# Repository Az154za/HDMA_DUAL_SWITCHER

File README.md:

# HDMA_DUAL_SWITCHER
This is 2 to 1 hdmi multiplexer that can switch screen visualisation between two pcs with a switch toggle using the TMDS261BPAG

# Schematic : 

# Routing :
The PCB was 4 layers 1 layer for GND , one layer for 5V

# 3D overview :

#BOM :

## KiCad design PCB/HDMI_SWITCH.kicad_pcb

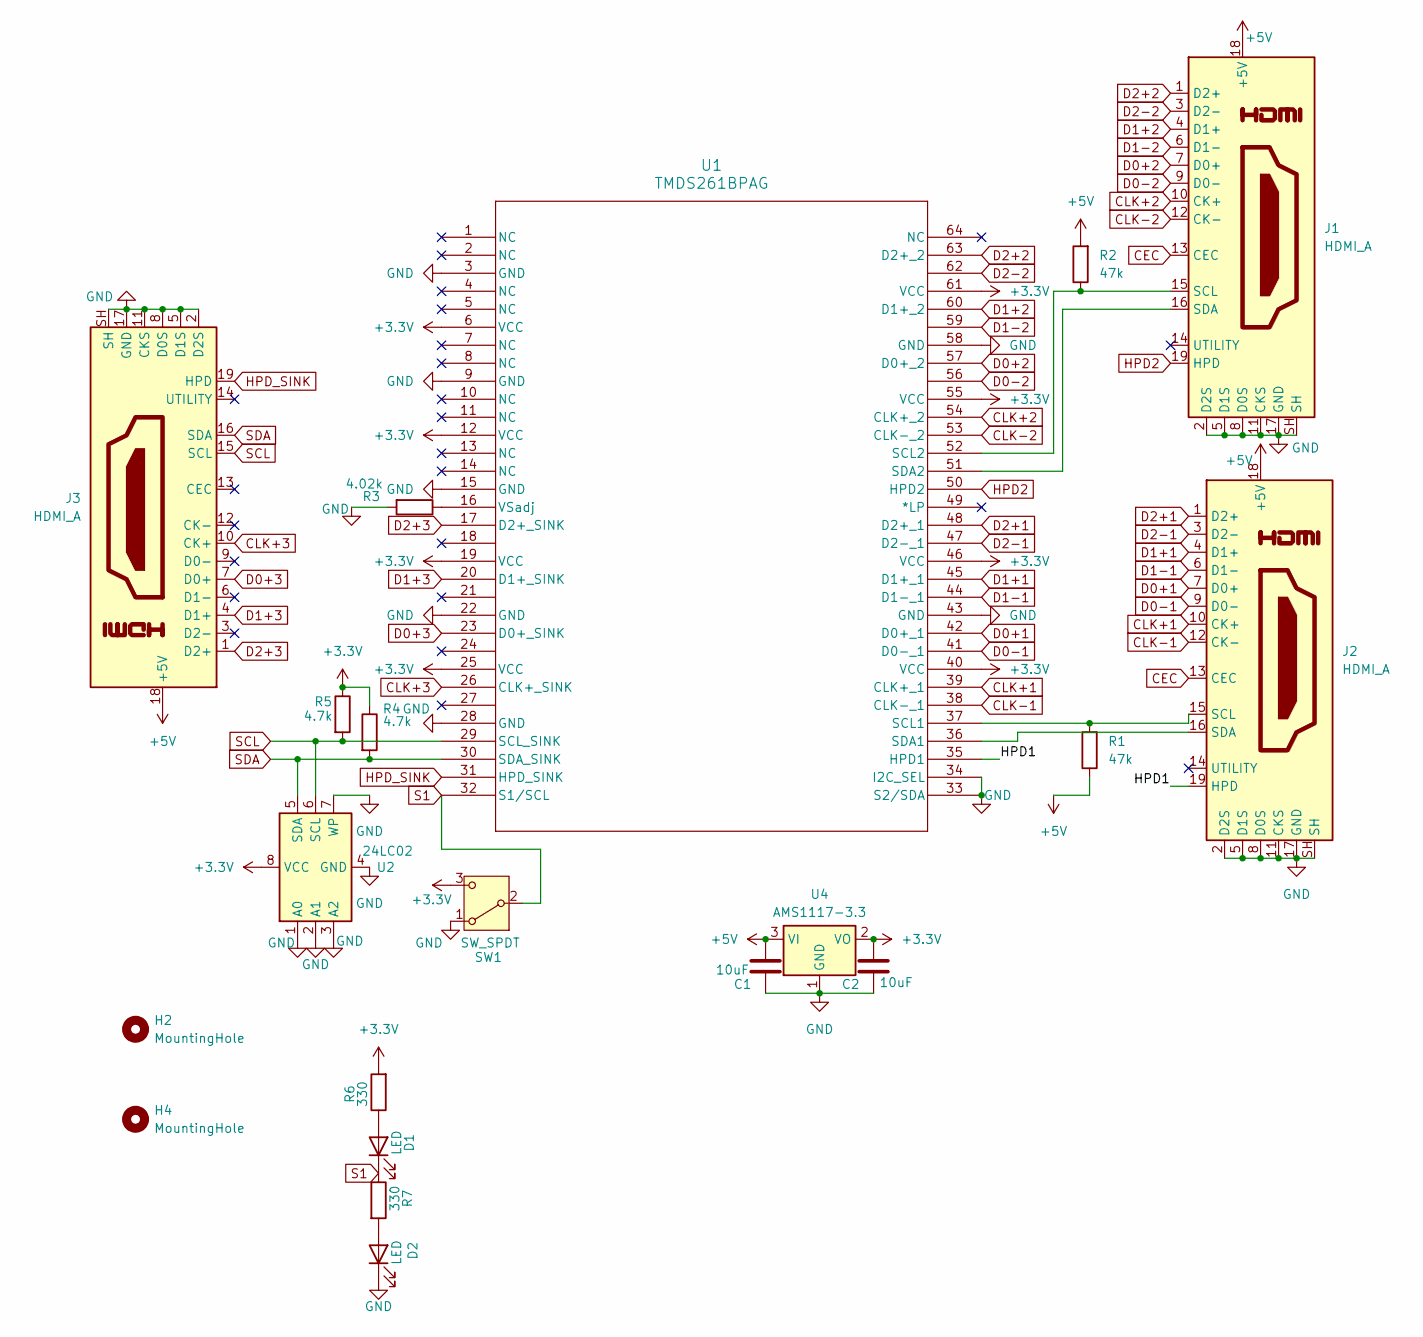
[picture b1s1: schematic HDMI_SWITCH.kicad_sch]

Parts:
C1, C2: 10uF; C_0805_2012Metric
D1, D2: LED; LED_0603_1608Metric
H2, H4: MountingHole; MountingHole_2.2mm_M2
J1, J2, J3: HDMI_A; HDMI_A_Amphenol_10029449-x01xLF_Horizontal
R1, R2: 47k; R_0402_1005Metric
R3: 4.02k; R_0402_1005Metric
R4, R5: 4.7k; R_0402_1005Metric
R6, R7: 330; R_0402_1005Metric
SW1: SW_SPDT; SW_SPDT_PCM12
U1: TMDS261BPAG; PAG64
U2: 24LC02; JEITA_SOIC-8_3.9x4.9mm_P1.27mm
U4: AMS1117-3.3; SOT-223-3_TabPin2

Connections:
+3.3V: C2.2, R4.1, R5.1, R6.2, SW1.3 (C), U1.6 (VCC), U1.12 (VCC), U1.19 (VCC), U1.25 (VCC), U1.40 (VCC), U1.46 (VCC), U1.55 (VCC), U1.61 (VCC), U2.8 (VCC), U4.2 (VO)
+5V: C1.2, J1.18 (+5V), J2.18 (+5V), J3.18 (+5V), R1.1, R2.2, U4.3 (VI)
/HPD1: J2.19 (HPD), U1.35 (HPD1)
CEC: J1.13 (CEC), J2.13 (CEC)
CLK+1: J2.10 (CK+), U1.39 (CLK+_1)
CLK+2: J1.10 (CK+), U1.54 (CLK+_2)
CLK+3: J3.10 (CK+), U1.26 (CLK+_SINK)
CLK-1: J2.12 (CK-), U1.38 (CLK-_1)
CLK-2: J1.12 (CK-), U1.53 (CLK-_2)
D0+1: J2.7 (D0+), U1.42 (D0+_1)
D0+2: J1.7 (D0+), U1.57 (D0+_2)
D0+3: J3.7 (D0+), U1.23 (D0+_SINK)
D0-1: J2.9 (D0-), U1.41 (D0-_1)
D0-2: J1.9 (D0-), U1.56
D1+1: J2.4 (D1+), U1.45 (D1+_1)
D1+2: J1.4 (D1+), U1.60 (D1+_2)
D1+3: J3.4 (D1+), U1.20 (D1+_SINK)
D1-1: J2.6 (D1-), U1.44 (D1-_1)
D1-2: J1.6 (D1-), U1.59
D2+1: J2.1 (D2+), U1.48 (D2+_1)
D2+2: J1.1 (D2+), U1.63 (D2+_2)
D2+3: J3.1 (D2+), U1.17 (D2+_SINK)
D2-1: J2.3 (D2-), U1.47 (D2-_1)
D2-2: J1.3 (D2-), U1.62
GND: C1.1, C2.1, D2.1 (K), J1.2 (D2S), J1.5 (D1S), J1.8 (D0S), J1.11 (CKS), J1.17 (GND), J1.SH, J2.2 (D2S), J2.5 (D1S), J2.8 (D0S), J2.11 (CKS), J2.17 (GND), J2.SH, J3.2 (D2S), J3.5 (D1S), J3.8 (D0S), J3.11 (CKS), J3.17 (GND), J3.SH, R3.2, SW1.1 (A), U1.3 (GND), U1.9 (GND), U1.15 (GND), U1.22 (GND), U1.28 (GND), U1.33 (S2/SDA), U1.34 (I2C_SEL), U1.43 (GND), U1.58 (GND), U2.1 (A0), U2.2 (A1), U2.3 (A2), U2.4 (GND), U2.7 (WP), U4.1 (GND)
HPD2: J1.19 (HPD), U1.50 (HPD2)
HPD_SINK: J3.19 (HPD), U1.31 (HPD_SINK)
unnamed: D1.2 (A), R6.1
unnamed: D2.2 (A), R7.2
unnamed: J1.15 (SCL), R2.1, U1.52 (SCL2)
unnamed: J1.16 (SDA), U1.51 (SDA2)
unnamed: J2.15 (SCL), R1.2, U1.37 (SCL1)
unnamed: J2.16 (SDA), U1.36 (SDA1)
unnamed: R3.1, U1.16 (VSadj)
S1: D1.1 (K), R7.1, SW1.2 (B), U1.32 (S1/SCL)
SCL: J3.15 (SCL), R5.2, U1.29 (SCL_SINK), U2.6 (SCL)
SDA: J3.16 (SDA), R4.2, U1.30 (SDA_SINK), U2.5 (SDA)

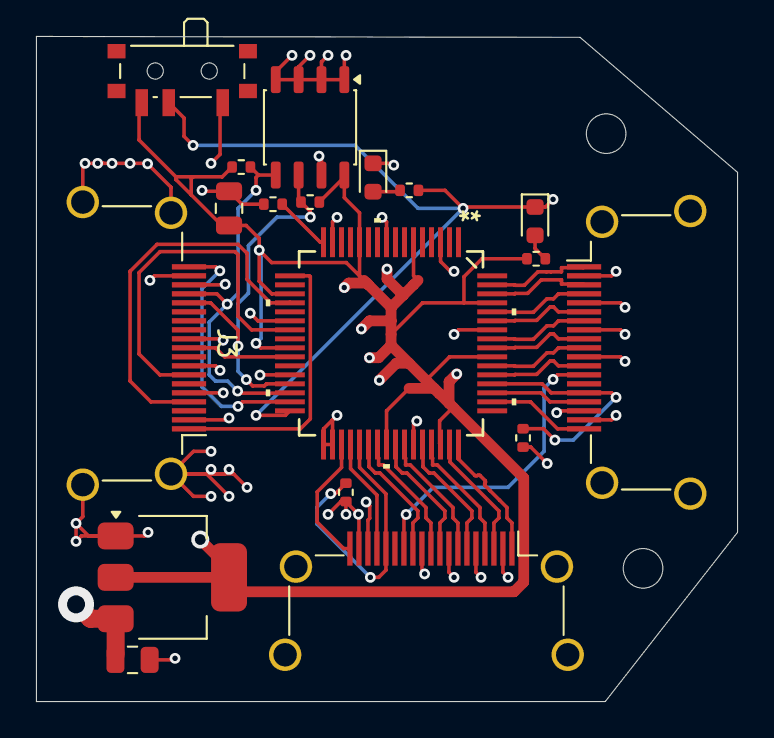
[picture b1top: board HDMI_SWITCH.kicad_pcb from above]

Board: 4 copper layers, 39.0 x 37.0 mm, 20 parts (0 on the bottom side), 37 nets.

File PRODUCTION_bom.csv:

Designator,Footprint,Quantity,Value,LCSC Part #,price,
"C1, C2",0805,2,10uF,C440198,0.0723,
"D1, D2",0603,2,LED,CC2290,0.012,
"J1, J2, J3",HDMI_A_Amphenol_10029449-x01xLF_Horizontal,3,HDMI_A,C428493,1.4366,
"R1, R2",0402,2,47k,C25792,0.00008,
R3,0402,1,4.02k,C43251,0.0006,
"R4, R5",0402,2,4.7k,C25900,0.00008,
"R6, R7",0402,2,330,C25104,0.0009,
SW1,SW_SPDT_PCM12,1,SW_SPDT,C221841,1.18,
U1,PAG64,1,TMDS261BPAG,C2869633,3.4,
U2,JEITA_SOIC-8_3.9x4.9mm_P1.27mm,1,24LC02,C2987256,0.07,
U3,SOIC-14_3.9x8.7mm_P1.27mm,1,74HC04,C5590,0.1594,
U4,SOT-223-3_TabPin2,1,AMS1117-3.3,C6186,0.2255,
